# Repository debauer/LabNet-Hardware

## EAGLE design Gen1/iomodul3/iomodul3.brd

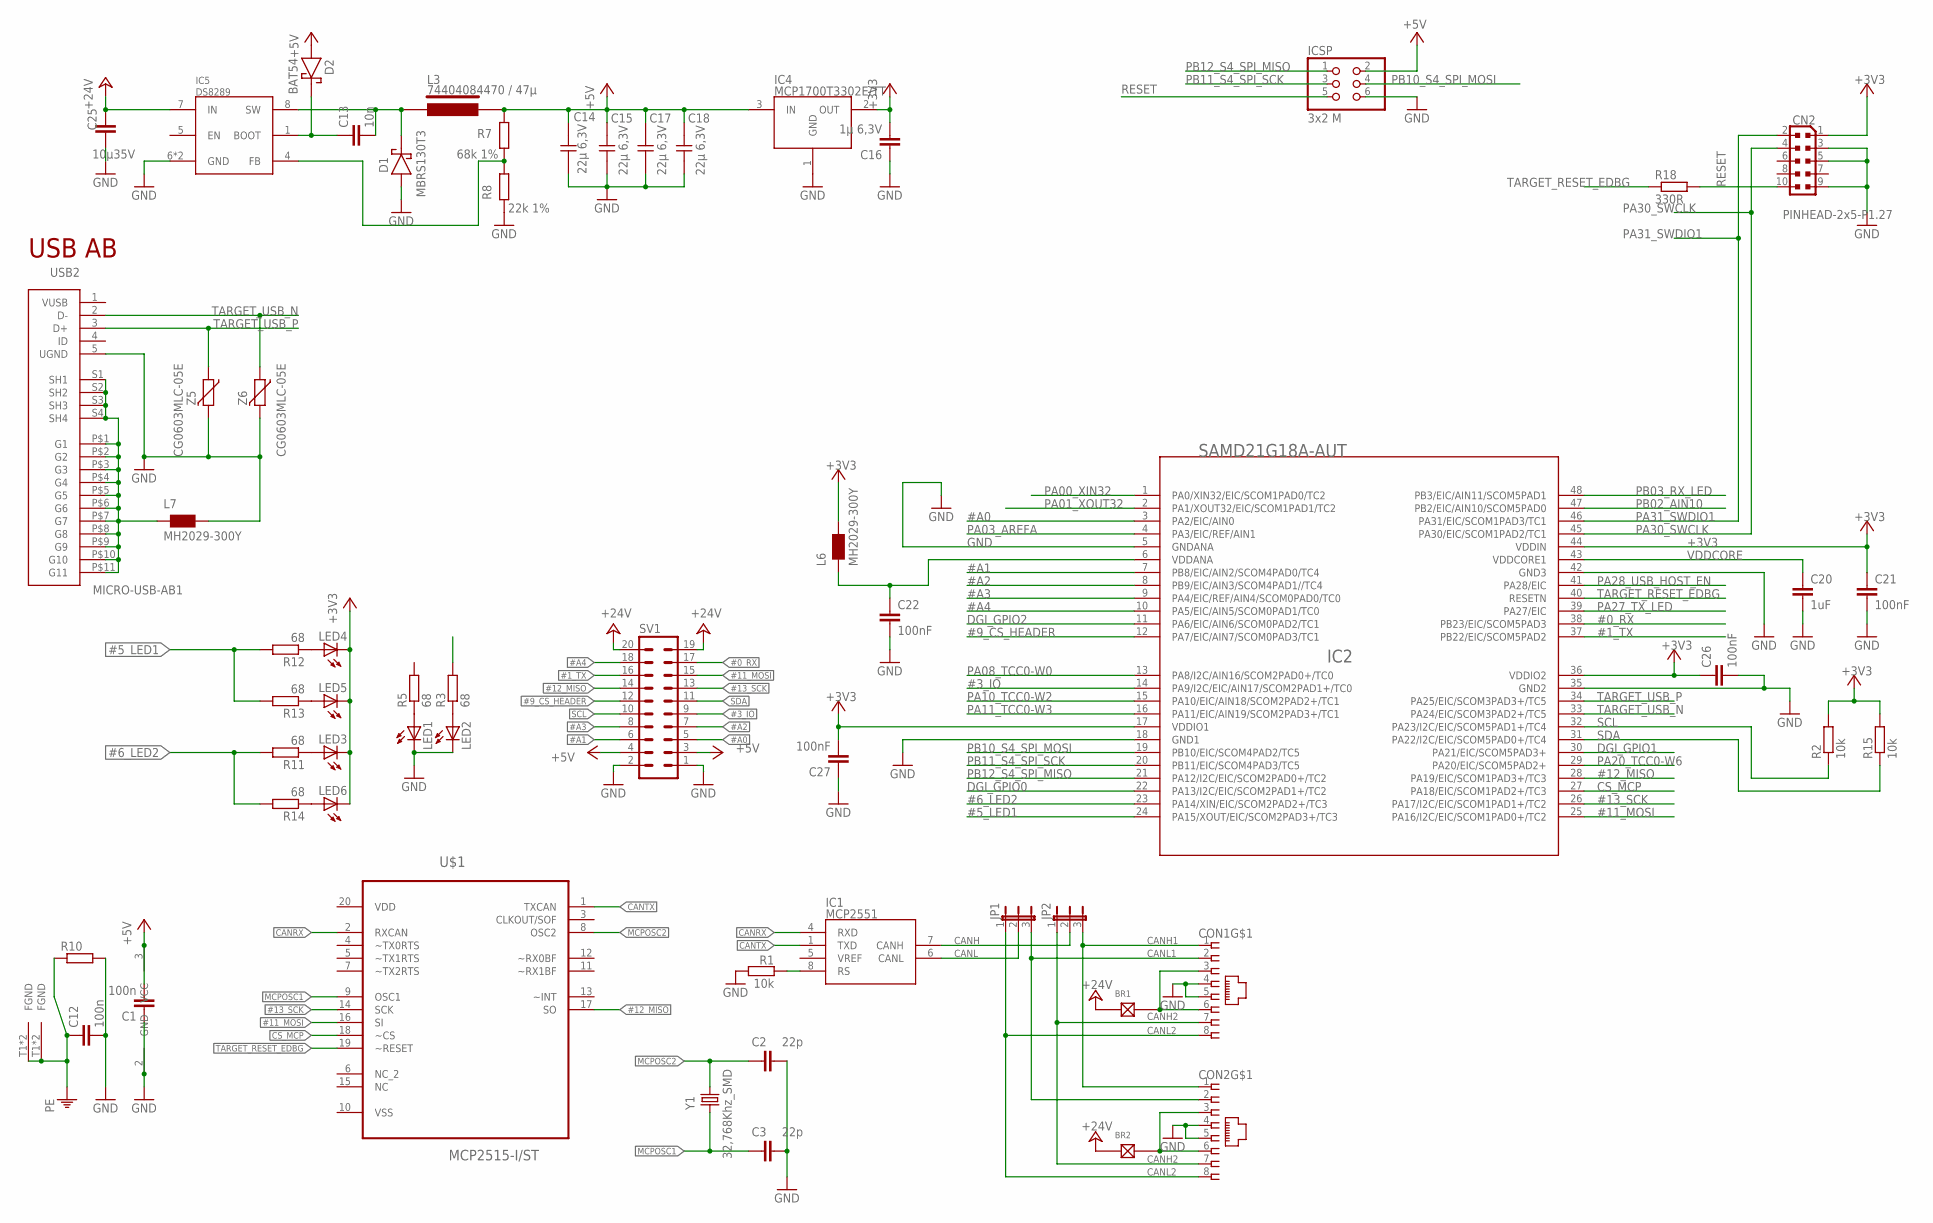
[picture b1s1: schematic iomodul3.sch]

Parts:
BR1, BR2: LÖTBRÜCKE-S; LÖTBRÜCKE
C1, C12: 100n; C0805
C2, C3: 22p; C0805
C13: 10n; C0805
C14, C15, C17, C18: 22µ 6,3V; 1210
C16: 1µ 6,3V; C1206
C20: 1uF; C0805
C21, C22, C26, C27: 100nF; C0805
C25: 10µ35V; C0805
CN2: PINHEAD-2x5-P1.27; PINHEAD-2X5-P127
CON1, CON2: MEBP_8-8G; MEBP
D1: MBRS130T3; SMB
D2: BAT54; SOT23/32
IC1: MCP2551; SO-8
IC2: SAMD21G18A-AUT; TQFP48-7X7
IC4: MCP1700T3302E/TT; SOT23
IC5: DS8289; SO8-POWERPAD
ICSP: 3x2 M; 2X03
JP1, JP2: JP2E; JP2
L3: 74404084470 / 47µ; WE-LQS
L6, L7: MH2029-300Y; 0805
LED1, LED2, LED3, LED4, LED5, LED6: LEDCHIPLED_0805; CHIPLED_0805
R1, R2, R15: 10k; R0805
R3, R5, R11, R12, R13, R14: 68; R0805
R7: 68k 1%; R0805
R8: 22k 1%; R0805
R10: R-EU_R0805; R0805
R18: 330R; R0805
SV1: MA10-2
U$1: MCP2515-I/ST; SOP65P640X110-20N
USB2: MICRO-USB-AB1; MCR-AB1-S-RA-SMT
Y1: 32,768Khz_SMD; RESONATOR_EPSON_FC_145
Z5, Z6: CG0603MLC-05E; CT/CN0603

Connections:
#0_RX: IC2.38 (PB23/EIC/SCOM5PAD3), SV1.17
#1_TX: IC2.37 (PB22/EIC/SCOM5PAD2), SV1.16
#3_IO: IC2.14 (PA9/I2C/EIC/AIN17/SCOM2PAD1+/TC0), SV1.9
#5_LED1: IC2.24 (PA15/XOUT/EIC/SCOM2PAD3+/TC3), R12.2, R13.2
#6_LED2: IC2.23 (PA14/XIN/EIC/SCOM2PAD2+/TC3), R11.2, R14.2
#9_CS_HEADER: IC2.12 (PA7/EIC/AIN7/SCOM0PAD3/TC1), SV1.12
#11_MOSI: IC2.25 (PA16/I2C/EIC/SCOM1PAD0+/TC2), SV1.15, U$1.16 (SI)
#12_MISO: IC2.28 (PA19/EIC/SCOM1PAD3+/TC3), SV1.14, U$1.17 (SO)
#13_SCK: IC2.26 (PA17/I2C/EIC/SCOM1PAD1+/TC2), SV1.13, U$1.14 (SCK)
#A0: IC2.3 (PA2/EIC/AIN0), SV1.5
#A1: IC2.7 (PB8/EIC/AIN2/SCOM4PAD0/TC4), SV1.6
#A2: IC2.8 (PB9/EIC/AIN3/SCOM4PAD1//TC4), SV1.7
#A3: IC2.9 (PA4/EIC/REF/AIN4/SCOM0PAD0/TC0), SV1.8
#A4: IC2.10 (PA5/EIC/AIN5/SCOM0PAD1/TC0), SV1.18
+3V3: C16.2, C21.1, C26.1, C27.2, CN2.1, IC2.17 (VDDIO1), IC2.36 (VDDIO2), IC2.44 (VDDIN), IC4.2 (OUT), L6.2, LED3.C, LED4.C, LED5.C, LED6.C, R2.2, R15.2
+5V: C1.2, C14.2, C15.2, C17.2, C18.2, D2.1 (A), IC1.3 (VCC), IC4.3 (IN), ICSP.2, L3.P$2, R7.2, SV1.3, SV1.4
+24V: BR1.1, BR2.1, C25.2, IC5.7 (IN), SV1.19, SV1.20
CANH: IC1.7 (CANH), JP2.2
CANH1: CON1.1, CON2.1, JP2.3
CANH2: CON1.7, CON2.7, JP2.1
CANL: IC1.6 (CANL), JP1.2
CANL1: CON1.2, CON2.2, JP1.3
CANL2: CON1.8, CON2.8, JP1.1
CANRX: IC1.4 (RXD), U$1.2 (RXCAN)
CANTX: IC1.1 (TXD), U$1.1 (TXCAN)
CS_MCP: IC2.27 (PA18/EIC/SCOM1PAD2+/TC3), U$1.18 (~CS)
DGI_GPIO0: IC2.22 (PA13/I2C/EIC/SCOM2PAD1+/TC2)
DGI_GPIO1: IC2.30 (PA21/EIC/SCOM5PAD3+)
DGI_GPIO2: IC2.11 (PA6/EIC/AIN6/SCOM0PAD2/TC1)
GND: C1.1, C2.2, C3.2, C12.2, C14.1, C15.1, C16.1, C17.1, C18.1, C20.2, C21.2, C22.2, C25.1, C26.2, C27.1, CN2.3, CN2.5, CN2.9, CON1.4, CON1.5, CON2.4, CON2.5, D1.A, IC1.2 (GND), IC2.5 (GNDANA), IC2.18 (GND1), IC2.35 (GND2), IC2.42 (GND3), IC4.1 (GND), IC5.6 (GND), IC5.TP (GND), ICSP.6, L7.2, LED1.C, LED2.C, R1.2, R8.1, R10.2, SV1.1, SV1.2, USB2.5 (UGND), Z5.2, Z6.2
LED2: R3.2
MCPOSC1: C3.1, U$1.9 (OSC1), Y1.P$1 (1)
MCPOSC2: C2.1, U$1.8 (OSC2), Y1.P$2 (2)
unnamed: IC1.8 (RS), R1.1
unnamed: BR1.2, CON1.3, CON1.6
unnamed: LED2.A, R3.1
unnamed: L7.1, USB2.P$1 (G1), USB2.P$2 (G2), USB2.P$3 (G3), USB2.P$4 (G4), USB2.P$5 (G5), USB2.P$6 (G6), USB2.P$7 (G7), USB2.P$8 (G8), USB2.P$9 (G9), USB2.P$10 (G10), USB2.P$11 (G11), USB2.S1 (SH1), USB2.S2 (SH2), USB2.S3 (SH3), USB2.S4 (SH4)
unnamed: BR2.2, CON2.3, CON2.6
unnamed: LED1.A, R5.1
unnamed: LED5.A, R13.1
unnamed: LED6.A, R14.1
unnamed: LED4.A, R12.1
unnamed: LED3.A, R11.1
unnamed: C13.1, D2.3 (K), IC5.1 (BOOT)
unnamed: C13.2, D1.K, IC5.8 (SW), L3.P$1
unnamed: C22.1, IC2.6 (VDDANA), L6.1
unnamed: IC5.4 (FB), R7.1, R8.2
PA00_XIN32: IC2.1 (PA0/XIN32/EIC/SCOM1PAD0/TC2)
PA01_XOUT32: IC2.2 (PA1/XOUT32/EIC/SCOM1PAD1/TC2)
PA03_AREFA: IC2.4 (PA3/EIC/REF/AIN1)
PA08_TCC0-W0: IC2.13 (PA8/I2C/AIN16/SCOM2PAD0+/TC0)
PA10_TCC0-W2: IC2.15 (PA10/EIC/AIN18/SCOM2PAD2+/TC1)
PA11_TCC0-W3: IC2.16 (PA11/EIC/AIN19/SCOM2PAD3+/TC1)
PA20_TCC0-W6: IC2.29 (PA20/EIC/SCOM5PAD2+)
PA27_TX_LED: IC2.39 (PA27/EIC)
PA28_USB_HOST_EN: IC2.41 (PA28/EIC)
PA30_SWCLK: CN2.4, IC2.45 (PA30/EIC/SCOM1PAD2/TC1)
PA31_SWDIO1: CN2.2, IC2.46 (PA31/EIC/SCOM1PAD3/TC1)
PB02_AIN10: IC2.47 (PB2/EIC/AIN10/SCOM5PAD0)
PB03_RX_LED: IC2.48 (PB3/EIC/AIN11/SCOM5PAD1)
PB10_S4_SPI_MOSI: IC2.19 (PB10/EIC/SCOM4PAD2/TC5), ICSP.4
PB11_S4_SPI_SCK: IC2.20 (PB11/EIC/SCOM4PAD3/TC5), ICSP.3
PB12_S4_SPI_MISO: IC2.21 (PA12/I2C/EIC/SCOM2PAD0+/TC2), ICSP.1
PE: C12.1, CON1.T1 (FGND), CON1.T2 (FGND), CON2.T1 (FGND), CON2.T2 (FGND), R10.1
RESET: CN2.10, ICSP.5, R18.2
SCL: IC2.32 (PA23/I2C/EIC/SCOM5PAD1+/TC4), R2.1, SV1.10
SDA: IC2.31 (PA22/I2C/EIC/SCOM5PAD0+/TC4), R15.1, SV1.11
TARGET_RESET_EDBG: IC2.40 (RESETN), R18.1, U$1.19 (~RESET)
TARGET_USB_N: IC2.33 (PA24/EIC/SCOM3PAD2+/TC5), USB2.2 (D-), Z6.1
TARGET_USB_P: IC2.34 (PA25/EIC/SCOM3PAD3+/TC5), USB2.3 (D+), Z5.1
VDD: U$1.20 (VDD)
VDDCORE: C20.1, IC2.43 (VDDCORE1)
VSS: U$1.10 (VSS)
VUSB: USB2.1 (VUSB)

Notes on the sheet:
USB AB

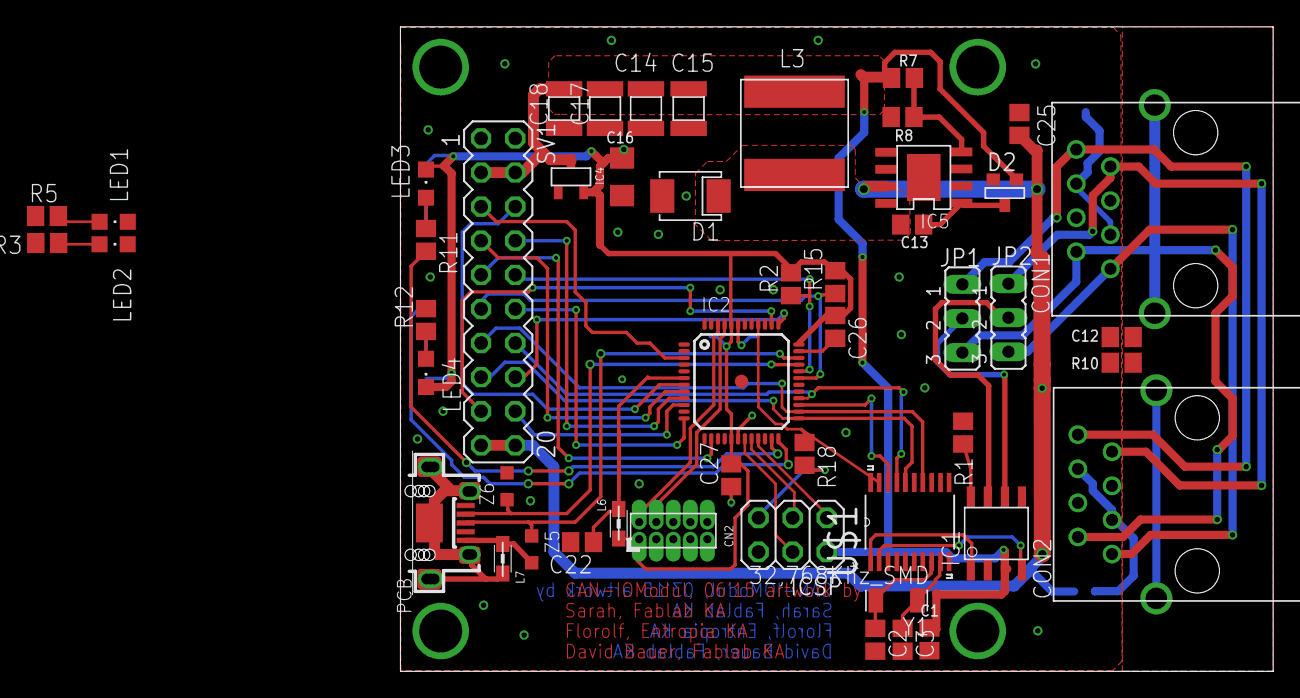
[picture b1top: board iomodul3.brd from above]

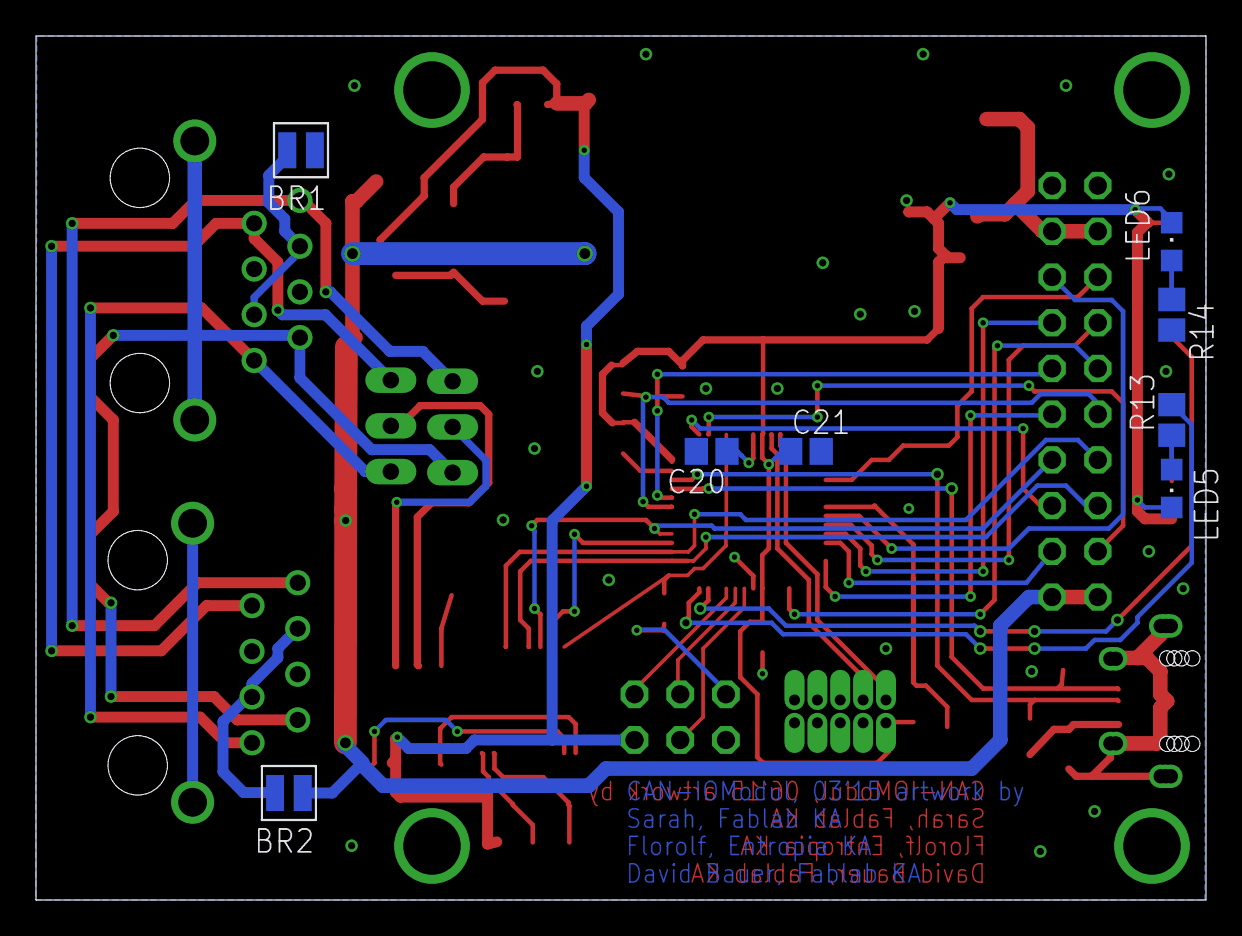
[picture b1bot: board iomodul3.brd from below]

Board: 2 copper layers, 65.0 x 48.0 mm, 58 parts (8 on the bottom side), 56 nets.

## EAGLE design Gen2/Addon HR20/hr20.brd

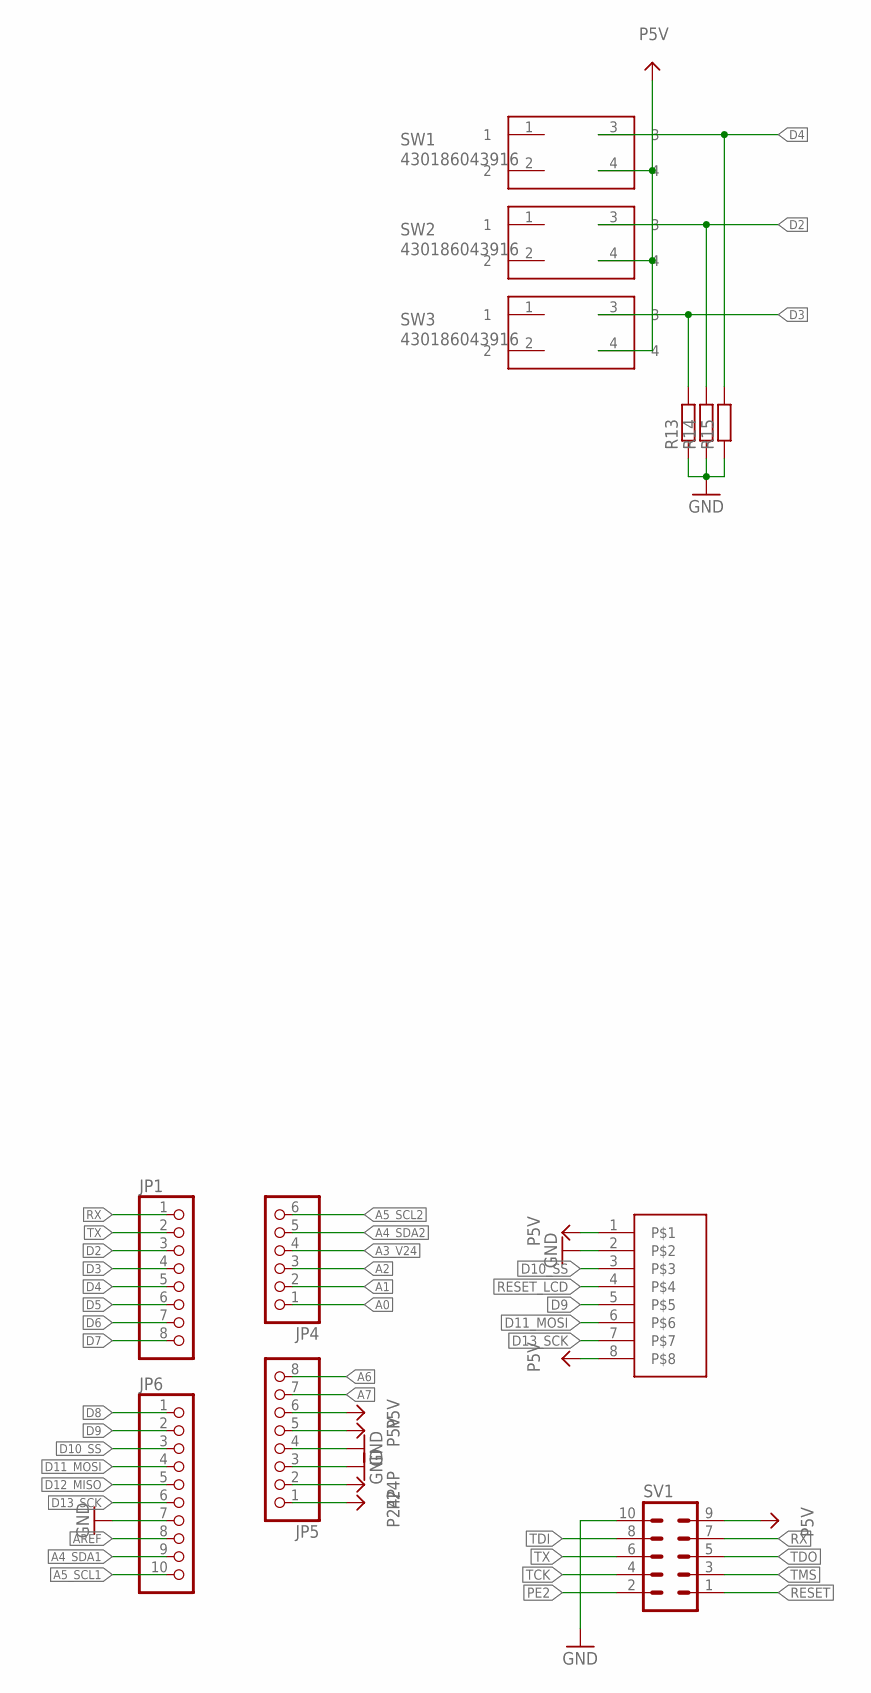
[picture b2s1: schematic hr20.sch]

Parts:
JP1, JP5: PINHD-1X8; 1X08
JP4: PINHD-1X6; 1X06
JP6: PINHD-1X10; 1X10
R13, R14, R15: R-EU_0207/10; 0207/10
SV1: ML10
SW1, SW2, SW3: 430186043916
U$2: 1.44-128X128

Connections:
A0: JP4.1
A1: JP4.2
A2: JP4.3
A3_V24: JP4.4
A4_SDA1: JP6.9
A4_SDA2: JP4.5
A5_SCL1: JP6.10
A5_SCL2: JP4.6
A6: JP5.8
A7: JP5.7
AREF: JP6.8
D2: JP1.3, R14.2, SW2.3
D3: JP1.4, R13.2, SW3.3
D4: JP1.5, R15.2, SW1.3
D5: JP1.6
D6: JP1.7
D7: JP1.8
D8: JP6.1
D9: JP6.2, U$2.5
D10_SS: JP6.3, U$2.3
D11_MOSI: JP6.4, U$2.6
D12_MISO: JP6.5
D13_SCK: JP6.6, U$2.7
GND: JP5.3, JP5.4, JP6.7, R13.1, R14.1, R15.1, SV1.10, U$2.2
P5V: JP5.5, JP5.6, SV1.9, SW1.4, SW2.4, SW3.4, U$2.1, U$2.8
P24P: JP5.1, JP5.2
PE2: SV1.2
RESET: SV1.1
RESET_LCD: U$2.4
RX: JP1.1, SV1.7
TCK: SV1.4
TDI: SV1.8
TDO: SV1.5
TMS: SV1.3
TX: JP1.2, SV1.6

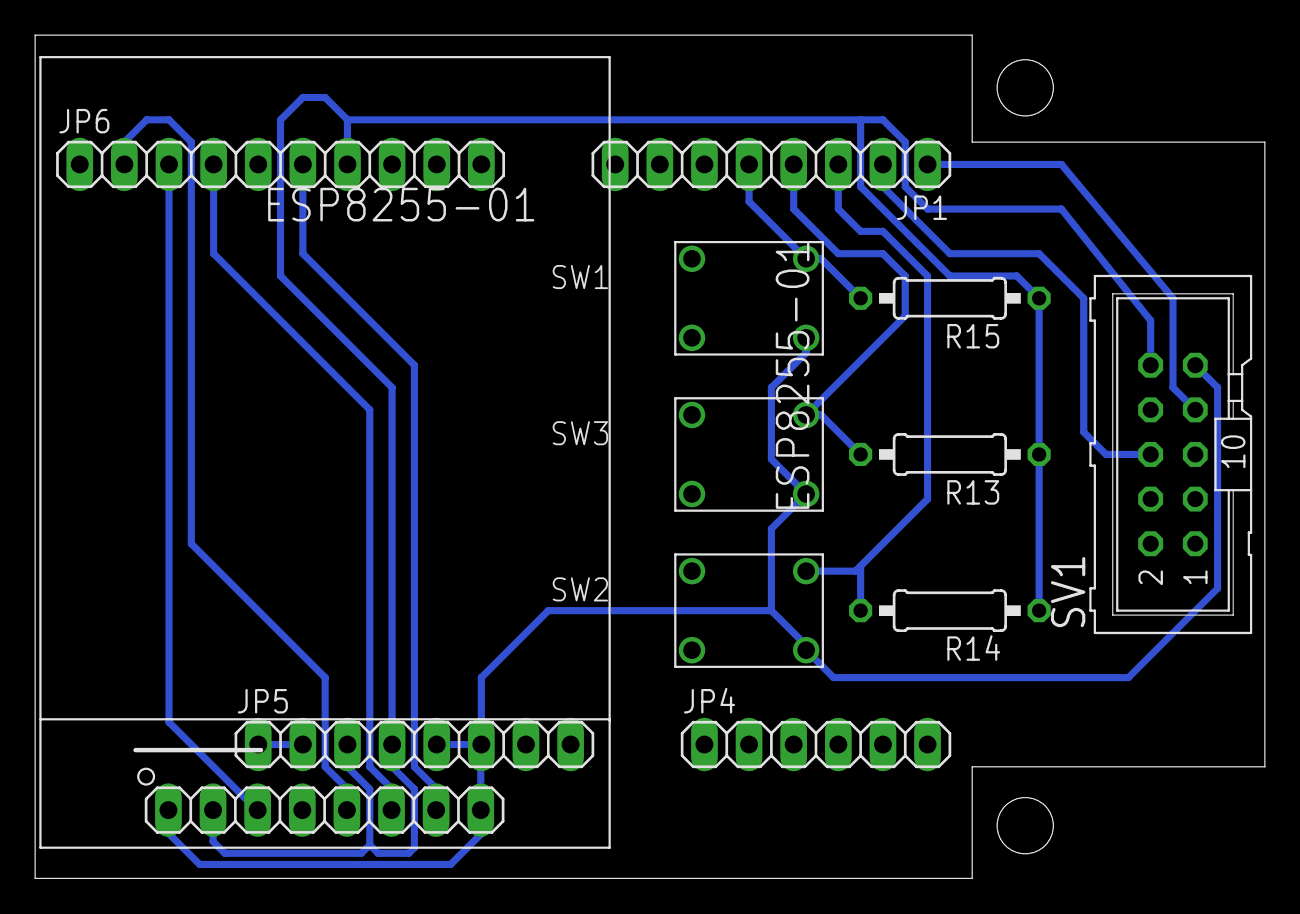
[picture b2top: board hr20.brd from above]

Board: 2 copper layers, 70.0 x 48.0 mm, 12 parts (0 on the bottom side), 12 nets.

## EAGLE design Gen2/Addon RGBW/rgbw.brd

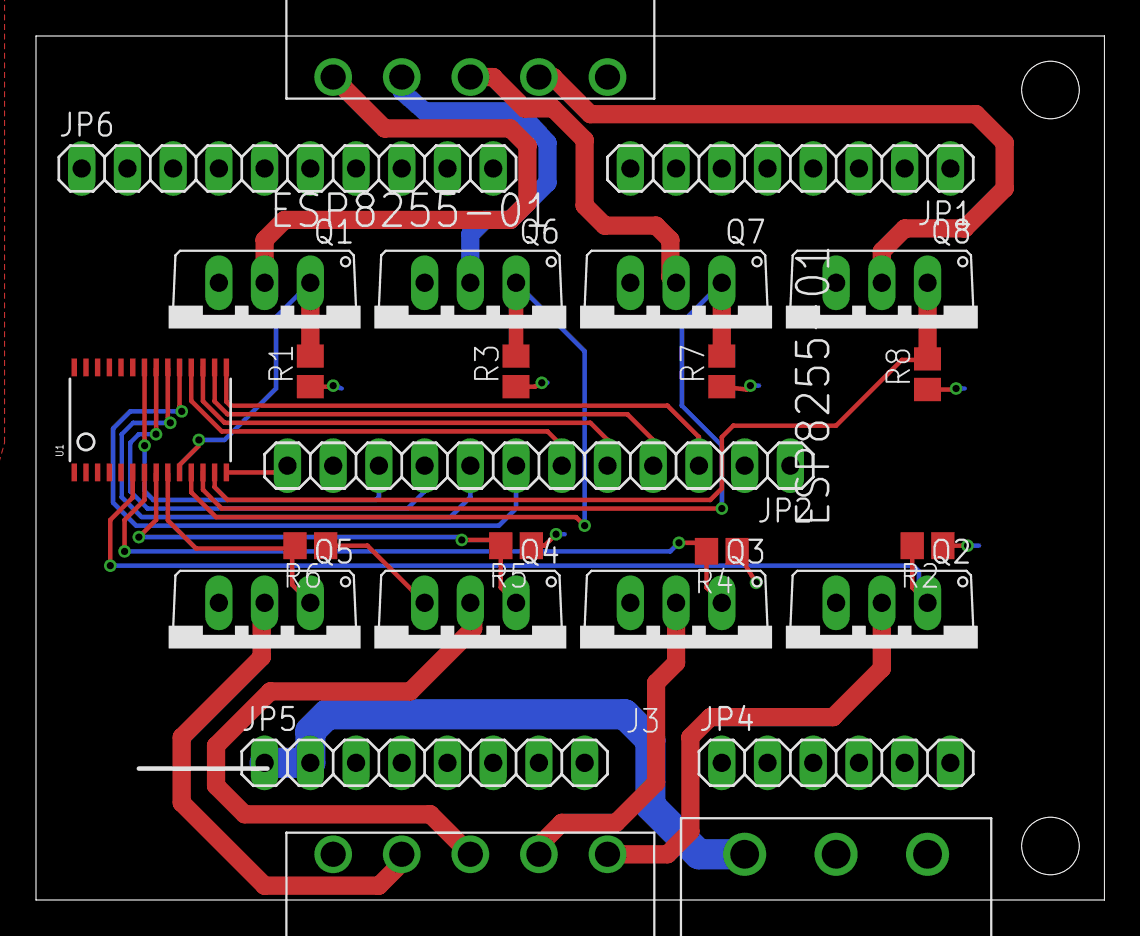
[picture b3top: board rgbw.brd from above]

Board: 2 copper layers, 59.4 x 48.0 mm, 25 parts (0 on the bottom side), 28 nets.

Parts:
J1, J2: 691322310005
J3: 691313510003
JP1, JP5: 1X08
JP2: 1X12
JP4: 1X06
JP6: 1X10
Q1, Q2, Q3, Q4, Q5, Q6, Q7, Q8: BUZ11; TO220V
R1, R2, R3, R4, R5, R6, R7, R8: R0805
U1: TSSOP28

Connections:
GND: J3.3, JP2.11, JP2.12, JP5.3, JP5.4, JP6.7, Q1.3, Q2.3, Q3.3, Q4.3, Q5.3, Q6.3, Q7.3, Q8.3, R1.1, R2.1, R3.1, R4.1, R5.1, R6.1, R7.1, R8.1, U1.14
LED0: Q2.1, R2.2, U1.6
LED1: Q3.1, R4.2, U1.7
LED2: Q4.1, R5.2, U1.8
LED3: Q5.1, R6.2, U1.9
LED4: Q1.1, R1.2, U1.10
LED5: Q6.1, R3.2, U1.11
LED6: Q7.1, R7.2, U1.12
LED7: Q8.1, R8.2, U1.13
LED8: JP2.3, U1.15
LED9: JP2.4, U1.16
LED10: JP2.5, U1.17
LED11: JP2.6, U1.18
LED12: JP2.7, U1.19
LED13: JP2.8, U1.20
LED14: JP2.9, U1.21
LED15: JP2.10, U1.22
unnamed: J2.1, Q2.2
unnamed: J2.2, Q3.2
unnamed: J1.3, Q7.2
unnamed: J2.3, Q4.2
unnamed: J2.4, Q5.2
unnamed: J1.4, Q8.2
unnamed: J1.1, Q1.2
unnamed: J1.2, Q6.2
P5V: JP5.5, JP5.6
P24P: J3.1, JP5.1, JP5.2
P24X: J1.5, J2.5, J3.2, JP2.1, JP2.2

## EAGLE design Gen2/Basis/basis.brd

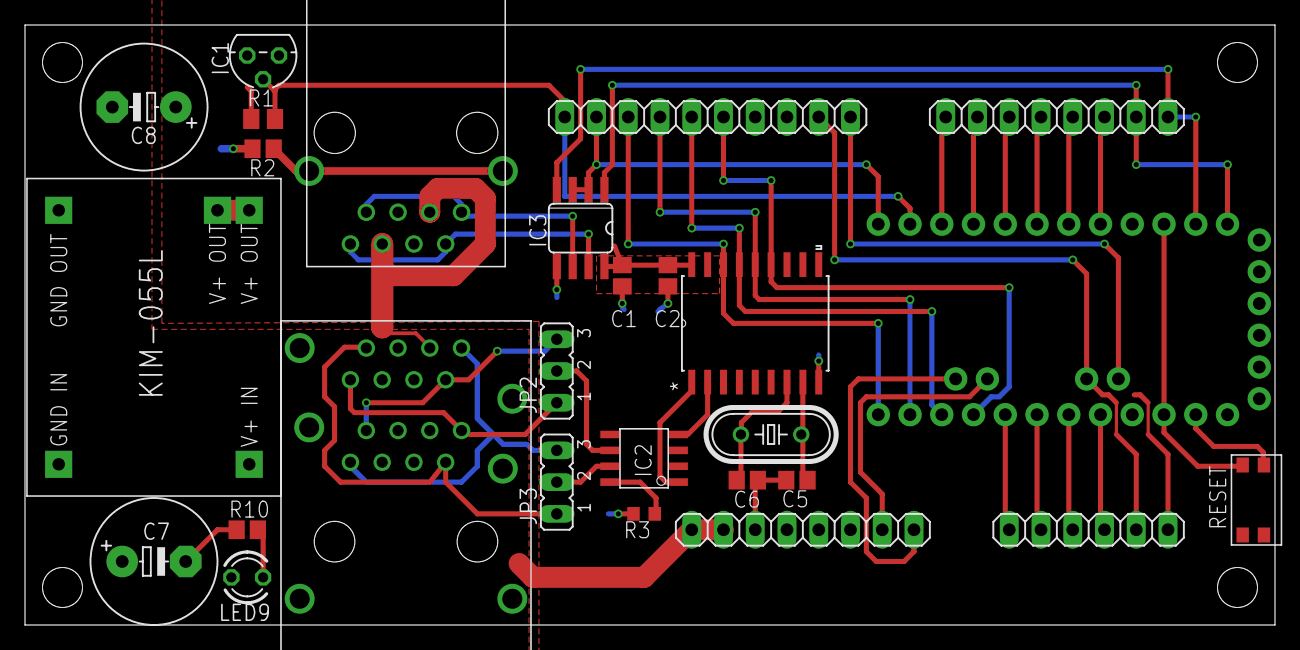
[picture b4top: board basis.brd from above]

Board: 2 copper layers, 100.0 x 48.0 mm, 27 parts (0 on the bottom side), 41 nets.

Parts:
C1, C2, C5, C6: C0805
C7, C8: E5-10,5
CON1: MEBP
IC1: DS1820TO92; TO-92
IC2: MCP2551; SO-8
IC3: MAX481CSA; SO08
JP1, JP5: 1X08
JP2, JP3: JP2
JP4: 1X06
JP6: 1X10
K4: 615016240521
LED9: LED3MM
MOD1: KIM-055L
Q1: HC49/S
R1: M0805
R2, R10: R0805
R3: 10k; R0603
RESET: 434351045816
U$1: ARDUINO_PRO_MINI
U$3: MCP2515-I/SO; SOIC127P1034X264-18N

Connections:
A0: JP4.1, U$1.17
A1: JP4.2, U$1.18
A2: JP4.3, U$1.19
A3_V24: JP4.4, U$1.20
A4_SDA: JP4.5, JP6.9, U$1.A4
A5_SCL: JP6.10, U$1.A5
A6: JP5.8, U$1.A6
A7: JP5.7, U$1.A7
CANH: IC2.7, JP3.2
CANH1: JP3.3, K4.A1, K4.B1
CANH2: JP3.1, K4.A7, K4.B7
CANL: IC2.6, JP2.2
CANL1: JP2.3, K4.A2, K4.B2
CANL2: JP2.1, K4.A8, K4.B8
CANRX: IC2.4, U$3.2
CANTX: IC2.1, U$3.1
D2: JP1.3, U$1.5
D3: JP1.4, U$1.6
D4: JP1.5, U$1.7
D5: JP1.6, U$1.8
D6: JP1.7, U$1.9
D7: JP1.8, U$1.10
D8: IC1.2, JP6.1, R1.1, U$1.11
D9: IC3.2, IC3.3, JP6.2, U$1.12
D10_SS: JP6.3, U$1.13, U$3.16
D11_MOSI: JP6.4, U$1.14, U$3.14
D12_MISO: JP6.5, U$1.15, U$3.15
D13_SCK: JP6.6, U$1.16, U$3.13
GND: C1.2, C2.2, C5.2, C6.2, C7.-, C8.-, CON1.4, CON1.5, IC1.1, IC3.5, JP5.3, JP5.4, JP6.7, K4.A4, K4.A5, K4.B4, K4.B5, MOD1.GNDIN, MOD1.GNDOUT, R2.1, R3.2, R10.1, RESET.2, U$1.4, U$1.23, U$3.9
MCP_OSC1: C5.1, Q1.1, U$3.8
MCP_OSC2: C6.1, Q1.2, U$3.7
unnamed: IC2.8, R3.1
unnamed: CON1.T1, CON1.T2, R2.2
unnamed: LED9.K, R10.2
P5V: C1.1, C2.1, C8.+, IC1.3, IC3.8, JP5.5, JP5.6, MOD1.V+OUT1, MOD1.V+OUT2, R1.2, U$1.21, U$3.18
P24P: C7.+, CON1.3, CON1.6, JP5.1, JP5.2, K4.A3, K4.A6, K4.B3, K4.B6, LED9.A, MOD1.V+IN
RESET: RESET.1, U$1.3, U$1.22
RS485_A: CON1.1, CON1.7, IC3.6
RS485_B: CON1.2, CON1.8, IC3.7
RX: IC3.4, JP1.1, U$1.2
TX: IC3.1, JP1.2, U$1.1

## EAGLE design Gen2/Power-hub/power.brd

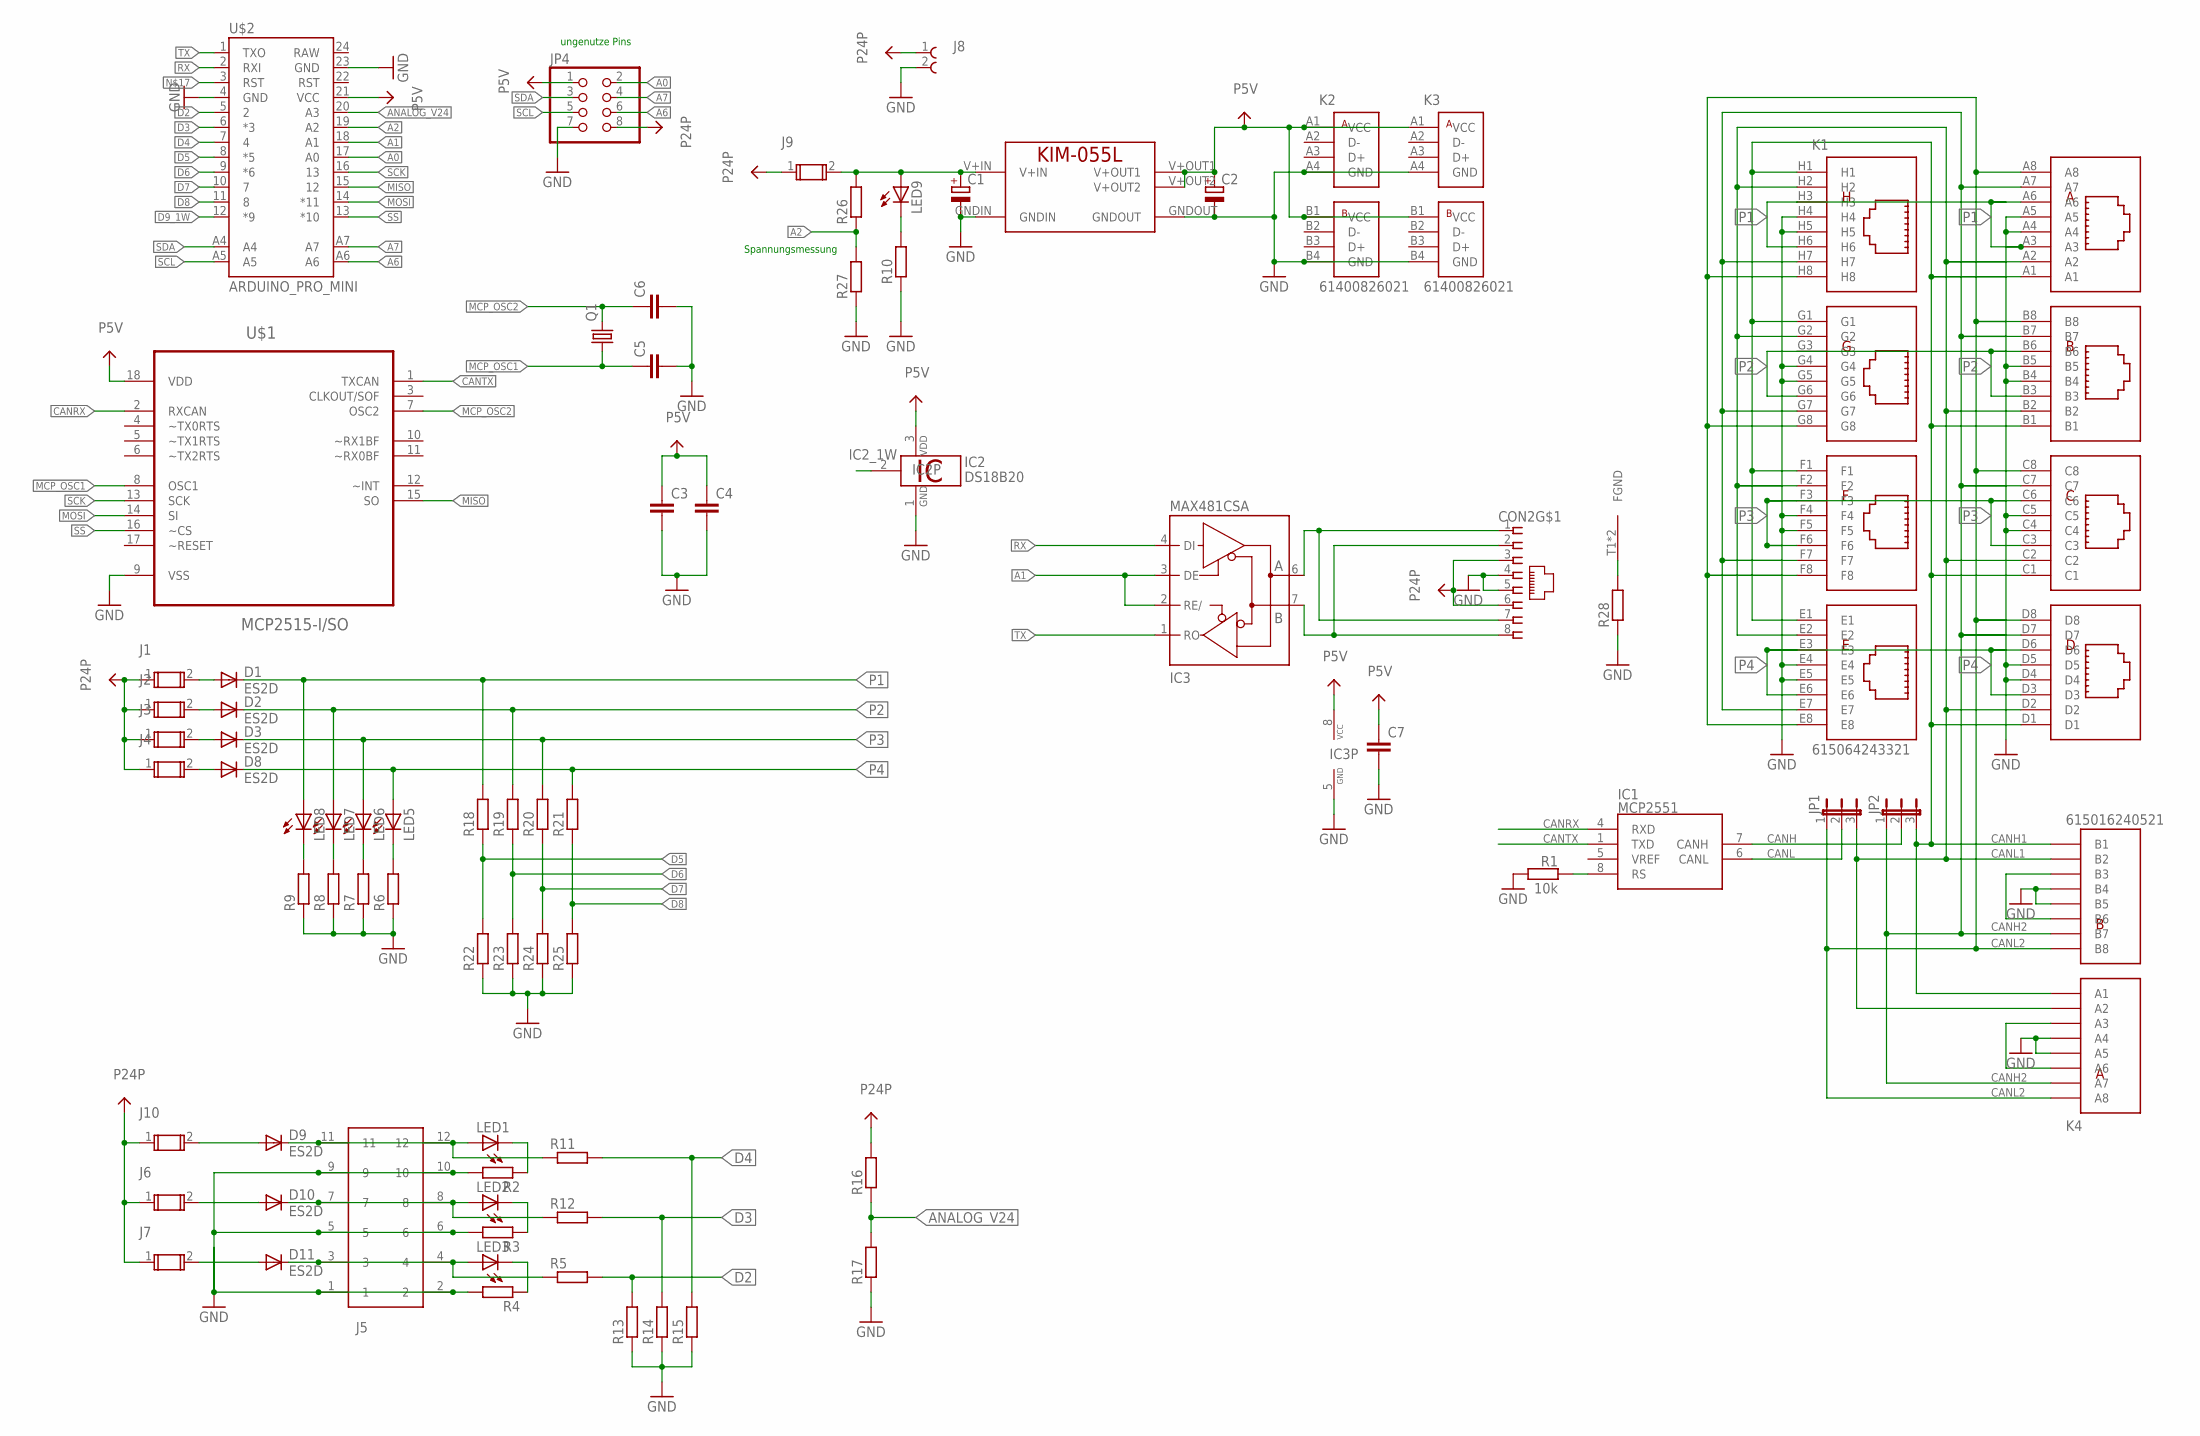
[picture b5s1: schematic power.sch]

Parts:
C1, C2: CPOL-EUE5-10.5; E5-10,5
C3, C4, C5, C6, C7: C-EUC0805; C0805
CON2: MEBP_8-8G; MEBP
D1, D2, D3, D8, D9, D10, D11: ES2D; SMB
IC1: MCP2551; SO-8
IC2: DS18B20; TO92-
IC3: MAX481CSA; SO08
J1, J2, J3, J4, J6, J7, J9, J10: 696101000002
J5: 691332510012
J8: 691312510002
JP1, JP2: JP2E; JP2
JP4: PINHD-2X4; 2X04
K1: 615064243321
K2, K3: 61400826021
K4: 615016240521
LED1, LED2, LED3, LED5, LED6, LED7, LED8, LED9: LED3MM
MOD1: KIM-055L
Q1: CRYSTALHC49S; HC49/S
R1: 10k; R0603
R2, R3, R4, R5, R6, R7, R8, R9, R10, R11, R12, R13, R14, R15, R16, R17, R18, R19, R20, R21, R22, R23, R24, R25, R26, R27, R28: R-EU_R0805; R0805
U$1: MCP2515-I/SO; SOIC127P1034X264-18N
U$2: ARDUINO_PRO_MINI

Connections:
A0: JP4.2, U$2.17 (A0)
A1: IC3.2 (RE/), IC3.3 (DE), U$2.18 (A1)
A2: R26.1, R27.2, U$2.19 (A2)
A6: JP4.6, U$2.A6
A7: JP4.4, U$2.A7
ANALOG_V24: R16.1, R17.2, U$2.20 (A3)
CANH: IC1.7 (CANH), JP2.2
CANH1: JP2.3, K1.A1, K1.B1, K1.C1, K1.D1, K1.E1, K1.F1, K1.G1, K1.H1, K4.A1, K4.B1
CANH2: JP2.1, K1.A7, K1.B7, K1.C7, K1.D7, K1.E7, K1.F7, K1.G7, K1.H7, K4.A7, K4.B7
CANL: IC1.6 (CANL), JP1.2
CANL1: JP1.3, K1.A2, K1.B2, K1.C2, K1.D2, K1.E2, K1.F2, K1.G2, K1.H2, K4.A2, K4.B2
CANL2: JP1.1, K1.A8, K1.B8, K1.C8, K1.D8, K1.E8, K1.F8, K1.G8, K1.H8, K4.A8, K4.B8
CANRX: IC1.4 (RXD), U$1.2 (RXCAN)
CANTX: IC1.1 (TXD), U$1.1 (TXCAN)
D2: R5.2, R13.2, U$2.5 (2)
D3: R12.2, R14.2, U$2.6 (*3)
D4: R11.2, R15.2, U$2.7 (4)
D5: R18.1, R22.2, U$2.8 (*5)
D6: R19.1, R23.2, U$2.9 (*6)
D7: R20.1, R24.2, U$2.10 (7)
D8: R21.1, R25.2, U$2.11 (8)
D9_1W: IC2.2 (1W), U$2.12 (*9)
GND: C1.-, C2.-, C3.2, C4.2, C5.2, C6.2, C7.2, CON2.4, CON2.5, IC2.1 (GND), IC3.5 (GND), J5.1, J5.2, J5.5, J5.6, J5.9, J5.10, J8.2, JP4.7, K1.A4, K1.A5, K1.B4, K1.B5, K1.C4, K1.C5, K1.D4, K1.D5, K1.E4, K1.E5, K1.F4, K1.F5, K1.G4, K1.G5, K1.H4, K1.H5, K2.A4 (GND), K2.B4 (GND), K3.A4 (GND), K3.B4 (GND), K4.A4, K4.A5, K4.B4, K4.B5, MOD1.GNDIN, MOD1.GNDOUT, R1.2, R2.2, R3.2, R4.2, R6.1, R7.1, R8.1, R9.1, R10.1, R13.1, R14.1, R15.1, R17.1, R22.1, R23.1, R24.1, R25.1, R27.1, R28.1, U$1.9 (VSS), U$2.4 (GND), U$2.23 (GND)
MCP_OSC1: C5.1, Q1.1, U$1.8 (OSC1)
MCP_OSC2: C6.1, Q1.2, U$1.7 (OSC2)
MISO: U$1.15 (SO), U$2.15 (12)
MOSI: U$1.14 (SI), U$2.14 (*11)
unnamed: IC1.8 (RS), R1.1
unnamed: K4.B3, K4.B6
unnamed: CON2.T1 (FGND), CON2.T2 (FGND), R28.2
unnamed: C1.+, J9.2, LED9.A, MOD1.V+IN, R26.2
unnamed: D1.A, J1.2
unnamed: K4.A3, K4.A6
unnamed: D2.A, J2.2
unnamed: LED9.K (C), R10.2
unnamed: D9.A, J10.2
unnamed: D11.A, J7.2
unnamed: D3.A, J3.2
unnamed: LED1.K (C), R2.1
unnamed: LED2.K (C), R3.1
unnamed: LED3.K (C), R4.1
unnamed: LED5.K (C), R6.2
unnamed: LED6.K (C), R7.2
unnamed: D8.A, J4.2
unnamed: LED7.K (C), R8.2
unnamed: LED8.K (C), R9.2
unnamed: D10.A, J6.2
unnamed: D9.C, J5.11, J5.12, LED1.A, R11.1
unnamed: D10.C, J5.7, J5.8, LED2.A, R12.1
unnamed: D11.C, J5.3, J5.4, LED3.A, R5.1
P1: D1.C, K1.A3, K1.A6, K1.H3, K1.H6, LED8.A, R18.2
P2: D2.C, K1.B3, K1.B6, K1.G3, K1.G6, LED7.A, R19.2
P3: D3.C, K1.C3, K1.C6, K1.F3, K1.F6, LED6.A, R20.2
P4: D8.C, K1.D3, K1.D6, K1.E3, K1.E6, LED5.A, R21.2
P5V: C2.+, C3.1, C4.1, C7.1, IC2.3 (VDD), IC3.8 (VCC), JP4.1, K2.A1 (VCC), K2.B1 (VCC), K3.A1 (VCC), K3.B1 (VCC), MOD1.V+OUT1, MOD1.V+OUT2, U$1.18 (VDD), U$2.21 (VCC)
P24P: CON2.3, CON2.6, J1.1, J2.1, J3.1, J4.1, J6.1, J7.1, J8.1, J9.1, J10.1, JP4.8, R16.2
RS485_A: CON2.1, CON2.7, IC3.6 (A)
RS485_B: CON2.2, CON2.8, IC3.7 (B)
RX: IC3.4 (DI), U$2.2 (RXI)
SCK: U$1.13 (SCK), U$2.16 (13)
SCL: JP4.5, U$2.A5
SDA: JP4.3, U$2.A4
SS: U$1.16 (~CS), U$2.13 (*10)
TX: IC3.1 (RO), U$2.1 (TXO)

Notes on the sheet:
ungenutze Pins
Spannungsmessung

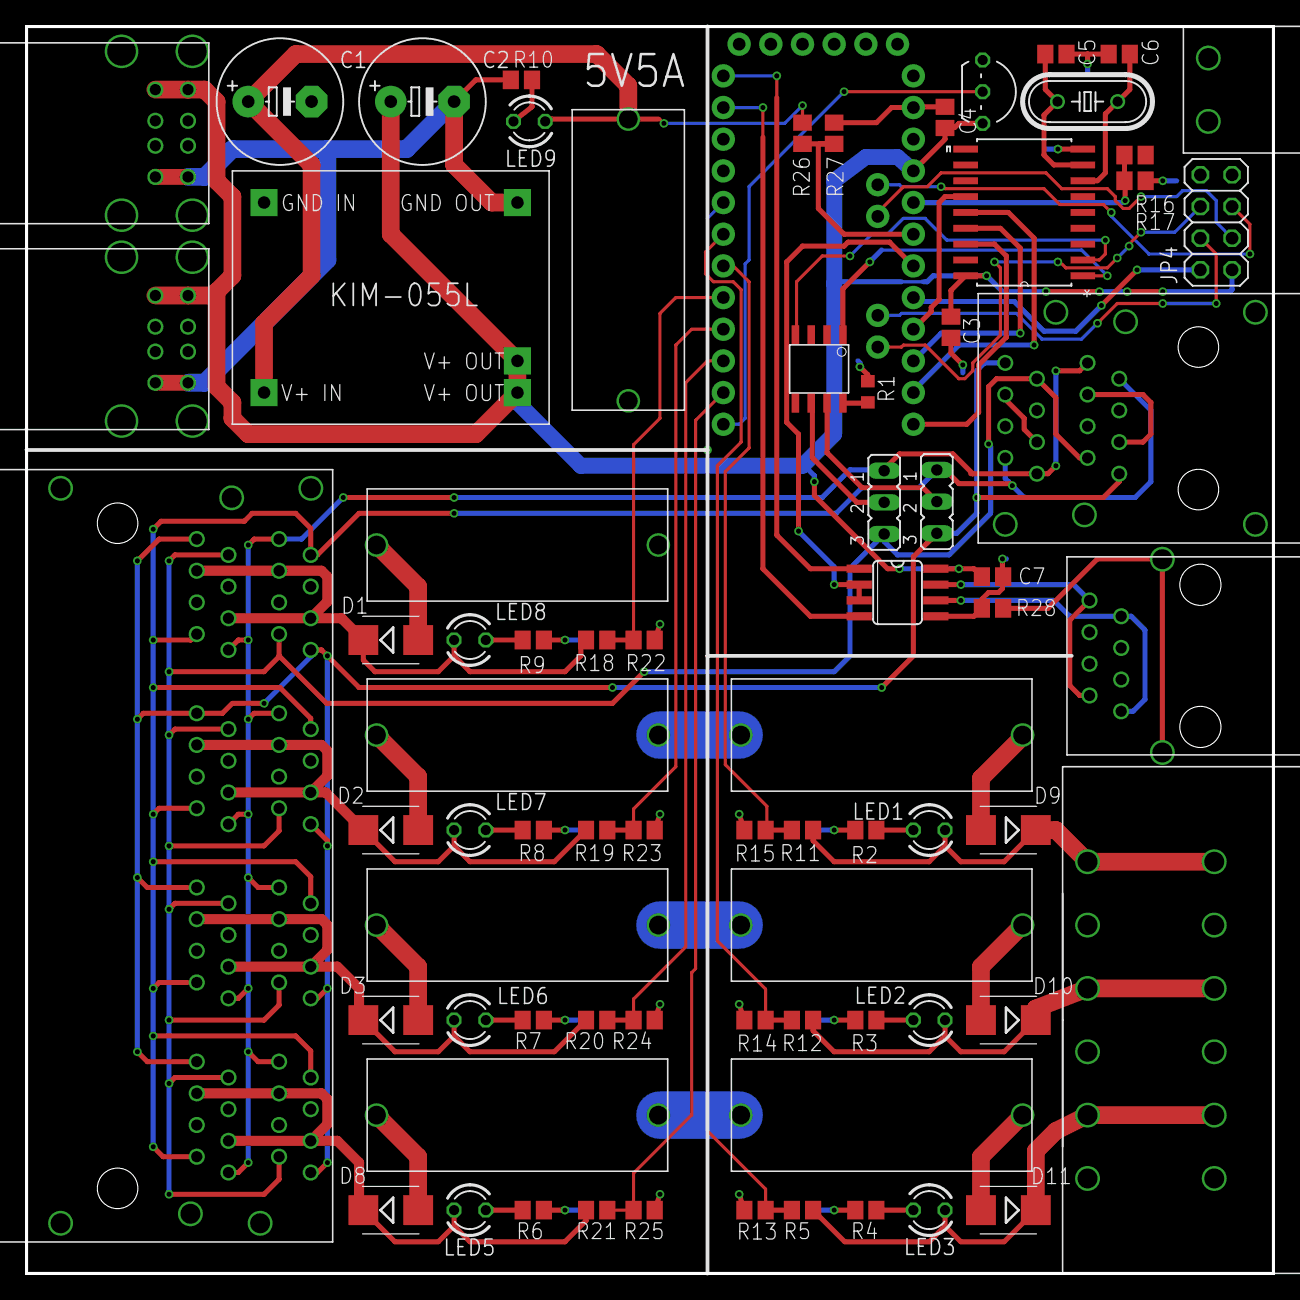
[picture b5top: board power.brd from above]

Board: 2 copper layers, 100.0 x 100.0 mm, 75 parts (0 on the bottom side), 64 nets.

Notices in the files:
parts and their libraries:
Wuerth_Elektronik_Switch: Copyright: Würth Elektronik
SparkFun-Boards: Licensing: Creative Commons ShareAlike 4.0 International - https://creativecommons.org/licenses/by-sa/4.0
